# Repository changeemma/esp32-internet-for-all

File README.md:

# ESP32 SPI Ring Connection Project

## Project Overview

This project implements a ring network topology using ESP32 microcontrollers connected via SPI (Serial Peripheral Interface). Each ESP32 board functions simultaneously as an SPI master and slave, creating a circular communication chain where data can flow bidirectionally through the network. This architecture enables efficient local communication within IoT nodes, supporting configurations from 2 to 5 boards in a single ring.

The system's unique feature is its dual-role approach: each board acts as a master for the next board and a slave for the previous one, enabling seamless data transmission throughout the network. One of the boards serves as an Access Point (AP), allowing the node to communicate with external networks while maintaining internal ring communication.

## Compatible Hardware
This project has been tested and verified to work with the following ESP32 boards:

- Espressif ESP32-DevKitC v4 (https://docs.espressif.com/projects/esp-idf/en/release-v4.2/esp32/hw-reference/esp32/get-started-devkitc.html)
- NodeMCU ESP32 WiFi + Bluetooth 4.2 IoT WROOM ESP32-S (https://docs.ai-thinker.com/_media/esp32/docs/nodemcu-32s_product_specification.pdf)

While the project may work with other ESP32 boards that have similar specifications, compatibility cannot be guaranteed without testing.

## Prerequisites

### ESP-IDF Installation
Before starting with this project, you need to install ESP-IDF v5.1.2. Follow these steps:

1. **Windows Installation**:
   - Download the ESP-IDF Windows Installer from the official ESP-IDF Releases page
   - Run the installer and follow the installation wizard
   - The installer will download and install:
     * ESP-IDF tools
     * Git
     * Python
     * Required build tools

2. **Linux/macOS Installation**:
   ```bash
   mkdir -p ~/esp
   cd ~/esp
   git clone -b v5.1.2 --recursive https://github.com/espressif/esp-idf.git
   cd esp-idf
   ./install.sh
   ```

3. **Set up ESP-IDF environment variables**:
   - Windows: Run `C:\esp\esp-idf\export.bat`
   - Linux/macOS: `. ~/esp/esp-idf/export.sh`

For detailed installation instructions, visit [ESP-IDF Get Started Guide](https://docs.espressif.com/projects/esp-idf/en/v5.1.2/esp32/get-started/index.html)

## Installing and Building the Project

1. Clone this repo and cd into it:
   ```bash
   git clone [repository-url]
   cd [project-directory]
   ```

2. Set up the ESP-IDF environment:
   ```bash
   get_idf
   ```

3. Build the project:
   ```bash
   idf.py build
   ```
   Note: Initial build will take some time while it compiles all required libraries.

## Board Configuration Options

The system supports between 2 to 5 ESP32 boards in a ring configuration:

### Possible Setups:
1. **2 boards**: Minimal configuration
   - Each ESP32 acts as both master and slave
   - Direct bidirectional communication

2. **3-4 boards**: Intermediate configuration

   Forms a ring where each board connects to its neighbors
   Required boards:

   One AP (Access Point) board
   Two or three boards from: North, South, East, or West

   Example (3 boards): AP + North + South
   Example (4 boards): AP + North + South + East

3. **5 boards**: Full configuration
   - Complete board setup with all roles:
     * North board
     * South board
     * East board
     * West board
     * AP (Access Point) board

### Board Roles
Each ESP32 in the ring must be configured with its specific role using the configuration pins (see GPIO Configuration section).

## GPIO - Connections for ESP32 - Physical ports ring connections

```
MASTER_GPIO_MOSI 23 <-> SLAVE_GPIO_MOSI 13
MASTER_GPIO_SCLK 18 <-> SLAVE_GPIO_SCLK 14
MASTER_GPIO_CS 5 <-> SLAVE_GPIO_CS 15
```

## IDF configuration: sdkconfig file

```bash
   get_idf menuconfig
```

Variables:
```
CONFIG_LWIP_L2_TO_L3_COPY=y (Enable copy between Layer2 and Layer3 packets)
CONFIG_LWIP_IP_FORWARD=y (Enable IP forwarding)
LWIP_IP_DEBUG=y (Only for debug)
```

## ESP32 Component Testing Guide

This guide explains how to add unit tests to your ESP32 component and how to run them using the ESP-IDF unit testing framework.

### Adding Tests to Your Component

1. Create a `test` directory in your component folder:

   ```
   your_component/
   ├── include/
   ├── your_component.c
   ├── CMakeLists.txt
   └── test/
       ├── test_your_component.c
       └── CMakeLists.txt
   ```

2. Write your test cases in `test_your_component.c`:

   ```c
   #include "unity.h"
   #include "your_component.h"

   TEST_CASE("Test case description", "[your_component]")
   {
       // Your test code here
       TEST_ASSERT_EQUAL(expected, your_function());
   }
   ```

3. Create a `CMakeLists.txt` file in the `test` directory:

   ```cmake
   idf_component_register(SRC_DIRS "."
                          INCLUDE_DIRS "."
                          REQUIRES your_component unity)
   ```

### Modifying the Unit Test App

1. Navigate to the unit test app directory:

   ```
   cd $IDF_PATH/tools/unit-test-app
   ```

2. Modify the `CMakeLists.txt` file to include your component's directory:

   ```cmake
   list(APPEND EXTRA_COMPONENT_DIRS "/path/to/your/components/directory")
   ```

   Replace `/path/to/your/components/directory` with the actual path to your components.

### Running the Tests

1. Navigate to the unit test app directory:

   ```
   cd $IDF_PATH/tools/unit-test-app
   ```

2. Configure the project:

   ```
   idf.py menuconfig
   ```

   Ensure that "Component config" -> "Unity unit testing library" -> "Enable unit tests" is enabled.

3. Build the unit test app:

   ```
   idf.py -T build all build
   ```
   or 

   ```
   idf.py -T build your_component build
   ```

4. Flash the app to your ESP32:

   ```
   idf.py -p PORT flash
   ```

   Replace `PORT` with your ESP32's port (e.g., `/dev/ttyUSB0`).

5. Run the tests:

   ```
   idf.py -p PORT monitor
   ```

   In the monitor, press 't' to see the test menu and select your tests to run.

## Further Reading

For more detailed information on ESP-IDF's build system and component structure, refer to the official ESP-IDF Programming Guide:

- [ESP-IDF Build System](https://docs.espressif.com/projects/esp-idf/en/stable/esp32/api-guides/build-system.html#cmake-file-globbing)
- [Unit Testing in ESP32](https://docs.espressif.com/projects/esp-idf/en/latest/esp32/api-guides/unit-tests.html)

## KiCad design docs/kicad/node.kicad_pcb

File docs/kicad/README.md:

# Espressif KiCad Library
Download and install Espressif Library on KiCAD following the instructions in https://github.com/espressif/kicad-libraries

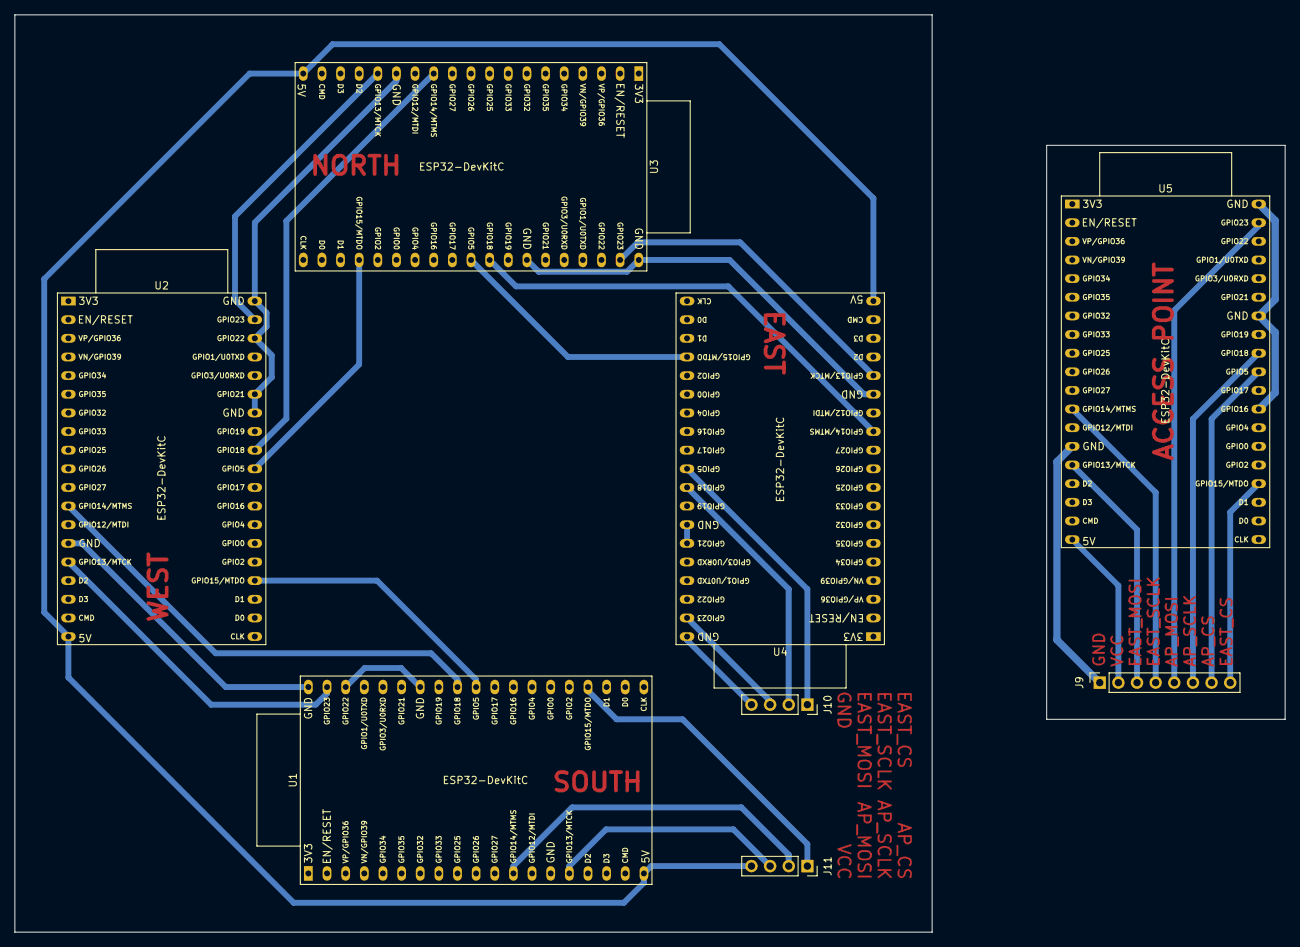
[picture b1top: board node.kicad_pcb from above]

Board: 2 copper layers, 173.1 x 125.0 mm, 8 parts (0 on the bottom side), 25 nets.

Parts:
J9: Conn_01x08; PinSocket_1x08_P2.54mm_Vertical
J10, J11: Conn_01x04_Pin; PinSocket_1x04_P2.54mm_Vertical
U1, U2, U3, U4, U5: ESP32-DevKitC

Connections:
/ap/B4_CS: J9.8, U5.23 (MTDO/GPIO15/ADC2_CH3)
/ap/B4_MOSI: J9.3, U5.15 (MTCK/GPIO13/ADC2_CH4)
/ap/B4_SCLK: J9.4, U5.12 (MTMS/GPIO14/ADC2_CH6)
/ap/B5_CS: J9.7, U5.29 (GPIO5)
/ap/B5_MOSI: J9.5, U5.37 (GPIO23)
/ap/B5_SCLK: J9.6, U5.30 (GPIO18)
/ap/VCC: J9.2, U5.19 (5V)
/main/B1_CS: U1.29 (GPIO5), U2.23 (MTDO/GPIO15/ADC2_CH3)
/main/B1_MOSI: U1.37 (GPIO23), U2.15 (MTCK/GPIO13/ADC2_CH4)
/main/B1_SCLK: U1.30 (GPIO18), U2.12 (MTMS/GPIO14/ADC2_CH6)
/main/B2_CS: U2.29 (GPIO5), U3.23 (MTDO/GPIO15/ADC2_CH3)
/main/B2_MOSI: U2.37 (GPIO23), U3.15 (MTCK/GPIO13/ADC2_CH4)
/main/B2_SCLK: U2.30 (GPIO18), U3.12 (MTMS/GPIO14/ADC2_CH6)
/main/B3_CS: U3.29 (GPIO5), U4.23 (MTDO/GPIO15/ADC2_CH3)
/main/B3_MOSI: U3.37 (GPIO23), U4.15 (MTCK/GPIO13/ADC2_CH4)
/main/B3_SCLK: U3.30 (GPIO18), U4.12 (MTMS/GPIO14/ADC2_CH6)
/main/B4_CS: J10.1, U4.29 (GPIO5)
/main/B4_MOSI: J10.3, U4.37 (GPIO23)
/main/B4_SCLK: J10.2, U4.30 (GPIO18)
/main/B5_CS: J11.1, U1.23 (MTDO/GPIO15/ADC2_CH3)
/main/B5_MOSI: J11.3, U1.15 (MTCK/GPIO13/ADC2_CH4)
/main/B5_SCLK: J11.2, U1.12 (MTMS/GPIO14/ADC2_CH6)
/main/VCC: J11.4, U1.19 (5V), U2.19 (5V), U3.19 (5V), U4.19 (5V)
GND: J10.4, U1.14 (GND), U1.32 (GND), U1.36 (GPIO22), U1.38 (GND), U2.14 (GND), U2.32 (GND), U2.33 (GPIO21), U2.36 (GPIO22), U2.38 (GND), U3.14 (GND), U3.32 (GND), U3.38 (GND), U4.14 (GND), U4.32 (GND), U4.33 (GPIO21), U4.38 (GND)
GND1: J9.1, U5.14 (GND), U5.27 (GPIO16), U5.32 (GND), U5.38 (GND)

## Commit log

2024-07-03 add build dir and sdkconfig to gitignore
2024-07-03 adding all files from previous repo
2024-07-04 use device component for main
2024-07-04 migrate from config comp to device comp
2024-07-04 use device instead of config in spi
2024-07-04 remove old config component
2024-07-04 ignore editor metadata
2024-07-04 somehow replaced old spi component
2024-07-04 separated spi components
2024-07-04 fixed some dependencies
2024-07-04 added tests, still wip
2024-07-24 Restructure spi components
2024-08-07 renaming components, hope this works
2024-08-08 renamed spi_netif module. somehow it works
2024-08-09 renamed a module (again), separated rx and tx
2024-08-09 another refactor
2024-08-09 this works
2024-08-09 moving stuff to ring_link component
2024-08-09 removing and moving stuff
2024-08-09 minor changes
2024-08-11 aaaa
2024-08-14 extract lowlevel implementation
2024-08-14 Add testing guide
2024-08-17 change Wi-Fi config
2024-08-20 Add heartbeat task
2024-08-20 refactor: Improve mutex handling and error checking in broadcast function
2024-08-20 refactor: process heartbeat packets without call to siblings
2024-08-20 docs: add buffer_type documentation
2024-08-23 feature: call handler when node comes online
2024-08-24 test: Add unit test for process_ring_link_payload
2024-08-24 Add Juan Pablo Quiroga as copyright holder in LICENSE
2024-09-07 adding physim as lowlevel impl, removing udp_spi
2024-09-07 removing udp_spi
2024-09-07 set info log level when OK
2024-09-07 troubleshooting physim
2024-09-10 Test: check mock calls
2024-09-10 Fix: cmake file
2024-09-10 Readme: update readme
2024-09-19 feature: add method to retrieve Wi-Fi IPv4 address
2024-09-20 Test: Route IPv4 packets
2024-09-22 Fix: return Wi-Fi ip address
2024-09-24 reduce log severity
2024-09-24 some refactors, exec online callback only once
2024-09-24 exec offline callback just once
2024-09-24 remove unused code
2024-09-28 extracted some methods, extracted default configs
2024-09-28 more refactors
2024-09-28 same for netif tx
2024-09-28 bugfix
2024-09-28 remove debug prints
2024-09-29 Fix: MAX_NUMBER_ROUTES called like macro
2024-09-29 Refactor: remove innecesary alloc
2024-09-30 Test: add ring_link_lowlevel
2024-10-10 Fix: ping station2station from diferents networks
2024-10-14 use config instead of device
2024-10-14 update gitignore
2024-10-14 moving ip functions to config, remove unused fxs
2024-10-14 rename functions
2024-10-14 get ipinfo from config
2024-10-14 remove ipv6
2024-10-14 remove unused function
2024-10-14 extract common code
2024-10-14 heartbeat refactor
2024-10-14 use log function
2024-10-14 rename config variables
2024-10-15 using incremental payload id, enhancing logs
2024-10-15 address review comment
2024-10-26 Feature: add RX queue
2024-10-26 Refactor: change SPI buffer size
2024-10-26 QA: Add script to measure performance
2024-10-27 Feature: add queues to process internal payloads and data payload
2024-11-01 Use task notification instead of queues, etc
2024-11-01 move heartbeat related stuff, use task notification for broadcast
2024-11-04 fix merge conflicts
2024-11-07 use task notification for heartbeat + refactors
2024-11-07 use task notification for broadcast
2024-11-07 move receive task
2024-11-07 refactor
2024-11-07 moved netif tasks to netif component
2024-11-07 move internal task to component
2024-11-07 renames and stuff
2024-11-20 fix merge conflicts from previous PR
2024-11-20 Adding KiCAD design
2024-11-22 Docs: refactor USB
2024-11-23 Docs: update kicad
2024-11-23 Docs: update kicad - reduce track width to 0.6mm
2024-11-25 Use pullup instead of pulldown
2024-11-26 update kicad model
2024-11-27 Shrink PCB + minor modifications
2024-11-27 minor adjustments
2024-11-27 fixed all DRC errors/warnings
2024-11-28 updated labels
2024-11-30 Docs: add software technical documentation
2024-11-30 Docs: add hardware technical documentation
2024-11-30 Refactor: delete unnecessary padding
2024-11-30 Docs: Update readme
2024-12-01 Docs: update software technical documentation
    s
2024-12-01 Improve user configuration: SPI
2024-12-10 draft
2024-12-13 Fix: read_config_bits()
2024-12-14 used 8mm routes 1mm clearance, having some gnd islands
2024-12-17 resolved all errors
2024-12-18 KiCad: Update images
2025-01-28 Update configuration - Add debug logs
2025-02-22 Use broadcast to emit heartbeat
2025-02-22 remove unused variable
2025-02-24 use rj45 to connect
2025-02-24 update docs
2025-03-01 Extract heartbeat to a separate component
2025-03-02 reset heartbeat_id after going offline
2025-03-03 move some operations to callbacks
2025-03-03 add s prefix to static variables
2025-03-03 add broadcast timeout
2025-03-03 small refactor
2025-03-03 adjust timeout
2025-04-15 Use interruptions for SPI transactions && Processing times are improved
2025-04-18 broadcast 2ms spi 15us
2025-04-23 DEBUG only main
2025-04-23 add broadcast
2025-05-11 debug
2025-05-11 config
2025-05-13 Add spi interruptions
2025-05-13 codigo medicion
2025-05-19 1500-bytes payloads are supported
2025-06-04 esto compila
2025-06-04 adding taskYIELD for all polling tasks
2025-06-04 removing unused function
2025-06-04 freeing after handler
2025-06-04 remove unused functions
2025-06-04 fix typo
2025-06-04 use spi_slave_queue_trans
2025-06-04 testing
2025-06-04 rollback core pined task
2025-06-04 use rx buffer directoy
2025-06-05 Revert "rollback core pined task"
    This reverts commit b053dae529cc5bf2d7e753074c682eb61a233671.
2025-06-06 some tweaks
2025-06-06 some other tweaks
2025-06-06 disable heartbeat
2025-06-06 adding test results!
2025-06-12 renaming variables and functions
2025-07-11 remove unused stuff
2025-08-26 added more code for perf tests
2025-08-27 heartbeat: adding success threshold + better logs
2025-09-08 remove unused vars
2025-09-08 spi tweaks
